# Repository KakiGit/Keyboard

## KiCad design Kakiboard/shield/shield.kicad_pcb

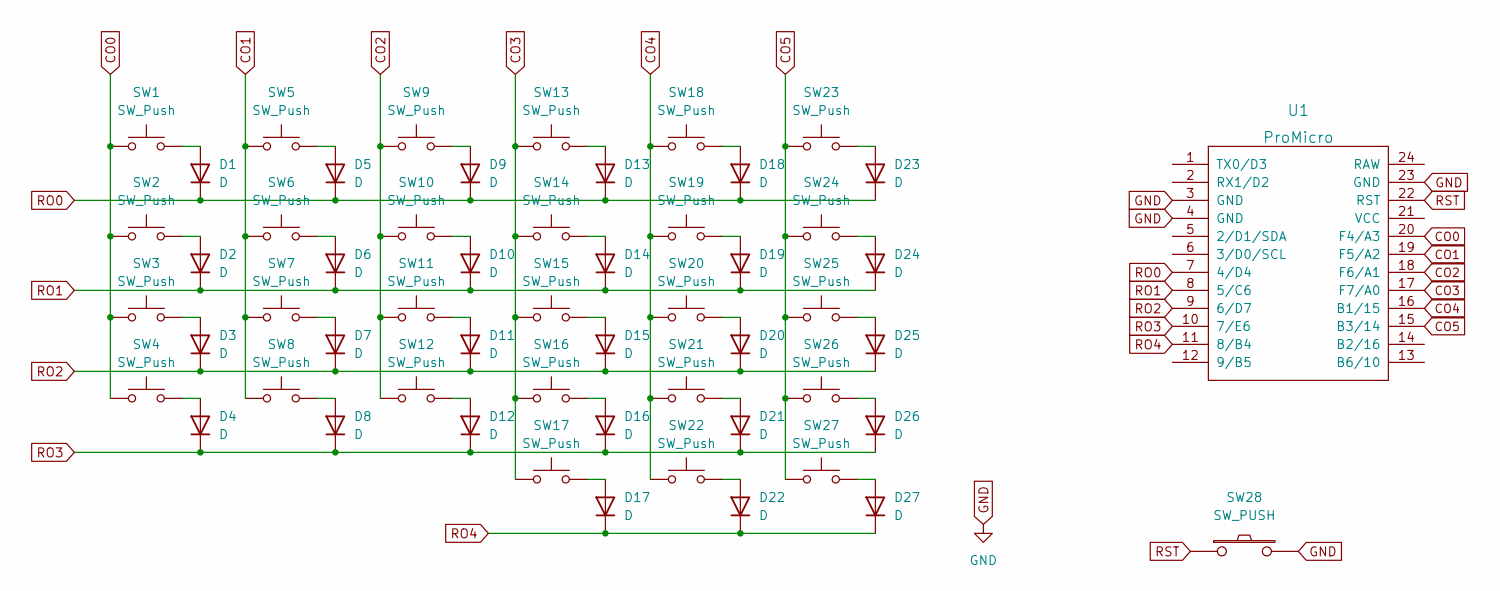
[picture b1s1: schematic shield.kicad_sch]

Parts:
D1, D2, D3, D4, D5, D6, D7, D8, D9, D10, D11, D12, D13, D14, D15, D16, D17, D18, D19, D20, D21, D22, D23, D24, D25, D26, D27: D; D3_SMD
SW1, SW2, SW3, SW4, SW5, SW6, SW7, SW8, SW9, SW10, SW11, SW12, SW13, SW14, SW15, SW16, SW17, SW18, SW19, SW20, SW21, SW22, SW23, SW24, SW25, SW26, SW27: SW_Push; Kailh_socket_PG1350_reversible
SW28: SW_PUSH; ResetSW
U1: ProMicro; KakiController

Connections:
CO0: SW1.1, SW2.1, SW3.1, SW4.1, U1.20 (F4/A3)
CO1: SW5.1, SW6.1, SW7.1, SW8.1, U1.19 (F5/A2)
CO2: SW9.1, SW10.1, SW11.1, SW12.1, U1.18 (F6/A1)
CO3: SW13.1, SW14.1, SW15.1, SW16.1, SW17.1, U1.17 (F7/A0)
CO4: SW18.1, SW19.1, SW20.1, SW21.1, SW22.1, U1.16 (B1/15)
CO5: SW23.1, SW24.1, SW25.1, SW26.1, SW27.1, U1.15 (B3/14)
GND: SW28.2, U1.3 (GND), U1.4 (GND), U1.23 (GND)
unnamed: D1.2 (A), SW1.2
unnamed: D2.2 (A), SW2.2
unnamed: D3.2 (A), SW3.2
unnamed: D4.2 (A), SW4.2
unnamed: D5.2 (A), SW5.2
unnamed: D6.2 (A), SW6.2
unnamed: D7.2 (A), SW7.2
unnamed: D8.2 (A), SW8.2
unnamed: D9.2 (A), SW9.2
unnamed: D10.2 (A), SW10.2
unnamed: D11.2 (A), SW11.2
unnamed: D12.2 (A), SW12.2
unnamed: D13.2 (A), SW13.2
unnamed: D14.2 (A), SW14.2
unnamed: D15.2 (A), SW15.2
unnamed: D16.2 (A), SW16.2
unnamed: D17.2 (A), SW17.2
unnamed: D18.2 (A), SW18.2
unnamed: D19.2 (A), SW19.2
unnamed: D20.2 (A), SW20.2
unnamed: D21.2 (A), SW21.2
unnamed: D22.2 (A), SW22.2
unnamed: D23.2 (A), SW23.2
unnamed: D24.2 (A), SW24.2
unnamed: D25.2 (A), SW25.2
unnamed: D26.2 (A), SW26.2
unnamed: D27.2 (A), SW27.2
RO0: D1.1 (K), D5.1 (K), D9.1 (K), D13.1 (K), D18.1 (K), D23.1 (K), U1.7 (4/D4)
RO1: D2.1 (K), D6.1 (K), D10.1 (K), D14.1 (K), D19.1 (K), D24.1 (K), U1.8 (5/C6)
RO2: D3.1 (K), D7.1 (K), D11.1 (K), D15.1 (K), D20.1 (K), D25.1 (K), U1.9 (6/D7)
RO3: D4.1 (K), D8.1 (K), D12.1 (K), D16.1 (K), D21.1 (K), D26.1 (K), U1.10 (7/E6)
RO4: D17.1 (K), D22.1 (K), D27.1 (K), U1.11 (8/B4)
RST: SW28.1, U1.22 (RST)

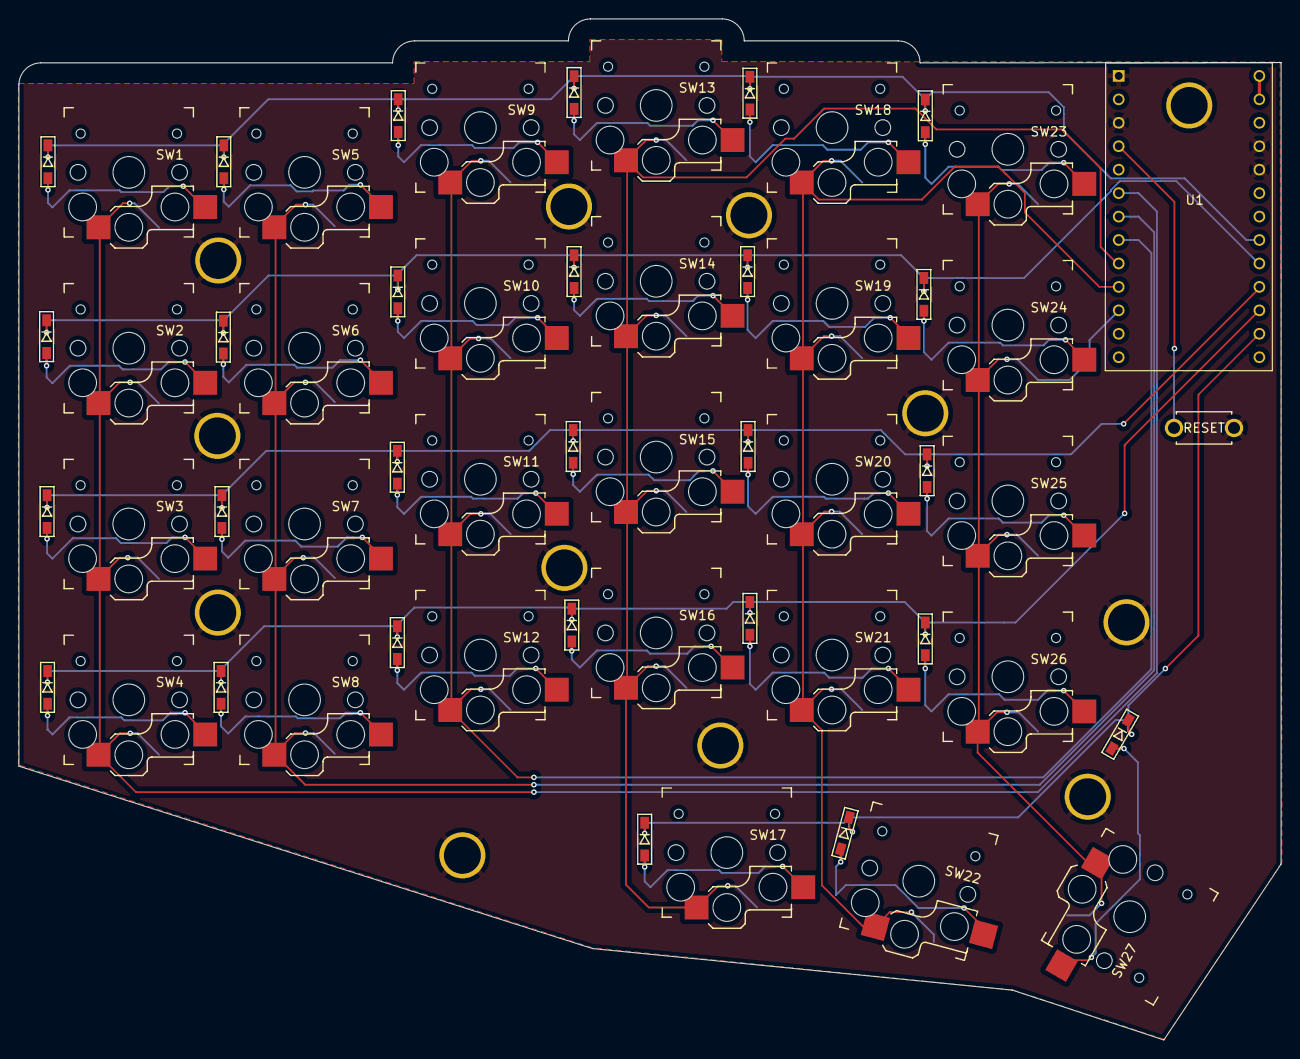
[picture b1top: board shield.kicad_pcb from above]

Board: 2 copper layers, 136.7 x 110.6 mm, 56 parts (0 on the bottom side), 40 nets.

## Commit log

2023-01-08 init
2023-01-12 update reset btn and wiring
2023-02-04 separate controller and shield
2023-02-04 add gitignore
2023-02-04 update config
2023-02-04 move CAD files into a separate folder
2023-02-04 change name for the keyboard
2023-02-04 finalize standalone keyboard
2023-02-05 change position for thumb keys
2023-03-06 Update cad from cab
